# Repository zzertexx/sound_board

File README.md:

# Soundboard — 16-key Macropad

A custom 16-key macropad built with a Seeed Studio XIAO RP2040, per-key LEDs, and a 0.91" OLED display. Made for [Hack Club](https://hackclub.com/).

---

## Features

- 16 MX-compatible switches in a 4×4 matrix
- Per-key SK6812 MINI-E RGB LEDs
- 0.91" OLED display
- Seeed Studio XIAO RP2040 microcontroller
- QMK firmware
- 3D printed case with sandwitch mounting

---

## Bill of Materials

| Component | Quantity |
|---|---|
| Seeed Studio XIAO RP2040 | 1 |
| MX-style switches | 16 |
| 1N4148 diodes | 16 |
| SK6812 MINI-E LEDs | 16 |
| 0.91" OLED display | 1 |
| DSA white blank keycaps | 16 |
| Resistor 330 ohms | 1 |
| M3x16mm screws | 4 |
| M3x5x4mm heatset inserts | 4 |

---

## Pin Assignment

| Pin | Signal |
|---|---|
| GP0 (PA02) | Row 0 |
| GP1 (PA4) | Row 1 |
| GP2 (PA10) | Row 2 |
| GP3 (PA11) | Row 3 |
| GP4 (PA8 SDA) | OLED SDA |
| GP5 (PA9 SCL) | OLED SCL |
| GP6 (PB08) | Column 0 |
| GP7 (PB09) | Column 1 |
| GP8 (PA7 SCK) | Column 2 |
| GP9 (PA5 MISO) | Column 3 |
| GP10 (PA6 MOSI) | LED Data |

---

## Schematic & PCB

Designed in KiCad 9.0. All source files are in the PCB directory.

- 4×4 keyboard matrix with diodes
- SK6812 MINI-E LEDs placed on bottom layer under each switch
- OLED connected via I2C
- Resistor on GP10 rail for LED stability

---

## Images

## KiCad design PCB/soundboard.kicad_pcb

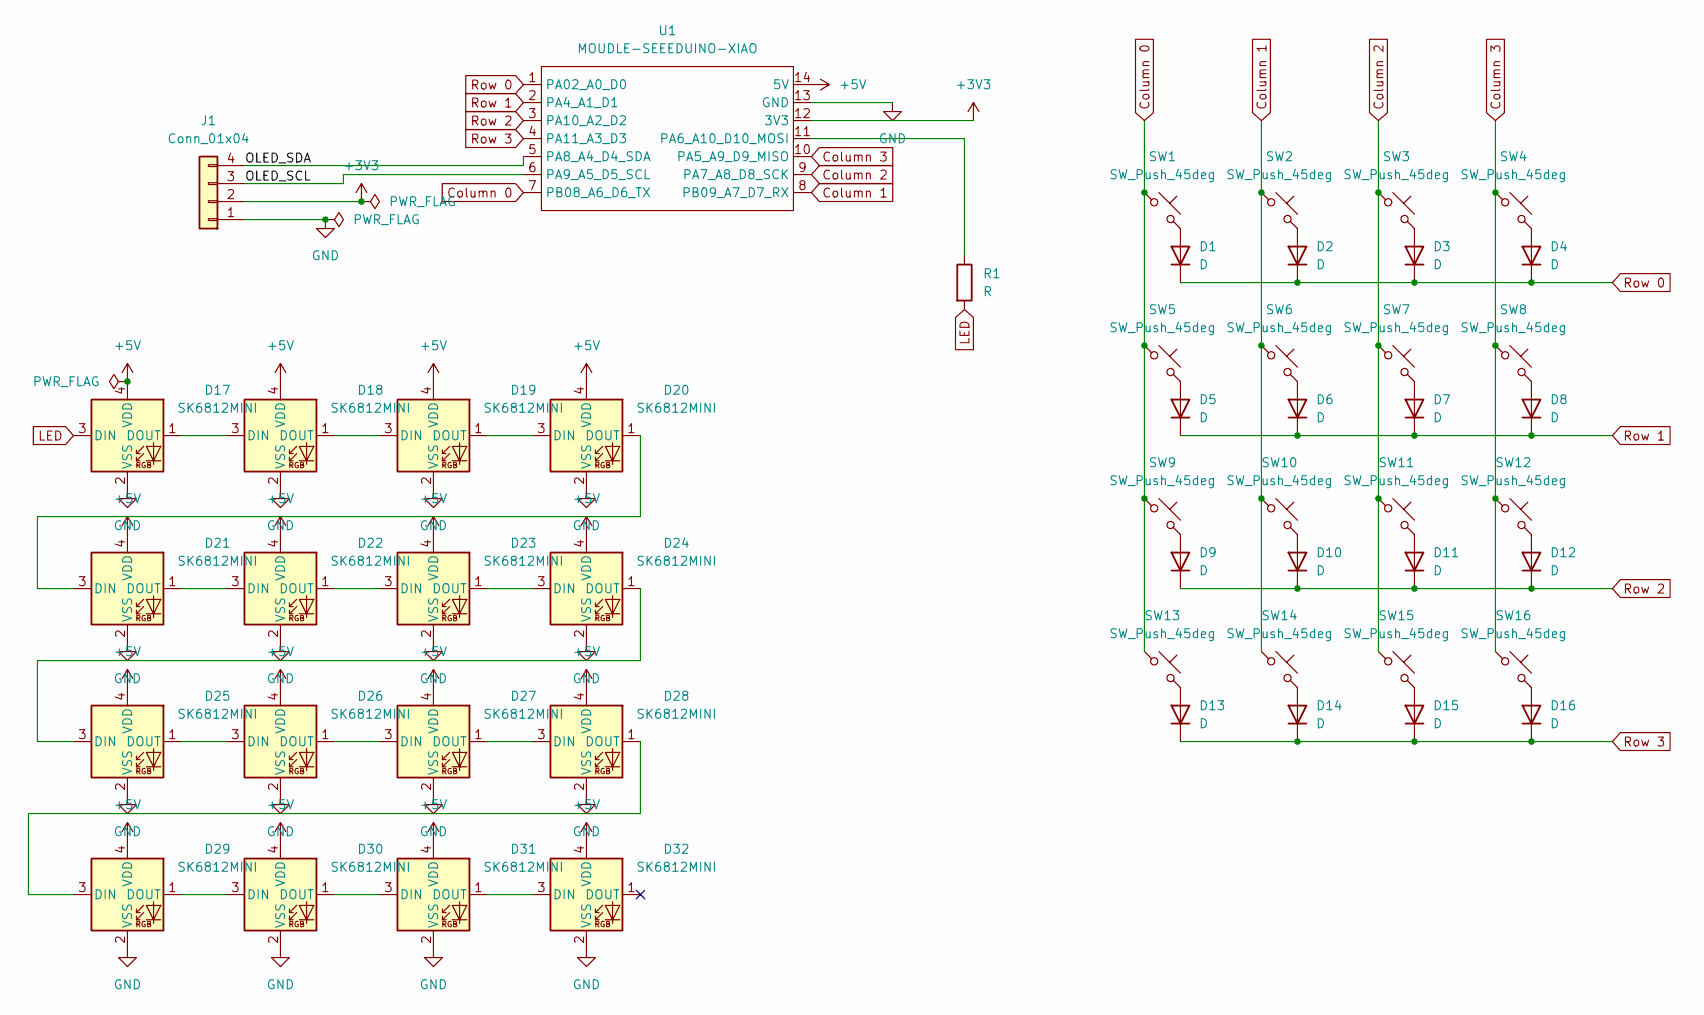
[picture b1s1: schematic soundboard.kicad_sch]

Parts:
D1, D2, D3, D4, D5, D6, D7, D8, D9, D10, D11, D12, D13, D14, D15, D16: D; D_DO-35_SOD27_P7.62mm_Horizontal
D17, D18, D19, D20, D21, D22, D23, D24, D25, D26, D27, D28, D29, D30, D31, D32: SK6812MINI; SK6812MINI-E_fixed
J1: Conn_01x04; PinHeader_1x04_P2.54mm_Vertical
R1: R; R_0805_2012Metric
SW1, SW2, SW3, SW4, SW5, SW6, SW7, SW8, SW9, SW10, SW11, SW12, SW13, SW14, SW15, SW16: SW_Push_45deg; SW_Cherry_MX_1.00u_PCB
U1: MOUDLE-SEEEDUINO-XIAO; XIAO-Generic-Hybrid-14P-2.54-21X17.8MM

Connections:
+3V3: J1.2, U1.12 (3V3)
+5V: D17.4 (VDD), D18.4 (VDD), D19.4 (VDD), D20.4 (VDD), D21.4 (VDD), D22.4 (VDD), D23.4 (VDD), D24.4 (VDD), D25.4 (VDD), D26.4 (VDD), D27.4 (VDD), D28.4 (VDD), D29.4 (VDD), D30.4 (VDD), D31.4 (VDD), D32.4 (VDD), U1.14 (5V)
/OLED_SCL: J1.3, U1.6 (PA9_A5_D5_SCL)
/OLED_SDA: J1.4, U1.5 (PA8_A4_D4_SDA)
Column 0: SW1.1, SW5.1, SW9.1, SW13.1, U1.7 (PB08_A6_D6_TX)
Column 1: SW2.1, SW6.1, SW10.1, SW14.1, U1.8 (PB09_A7_D7_RX)
Column 2: SW3.1, SW7.1, SW11.1, SW15.1, U1.9 (PA7_A8_D8_SCK)
Column 3: SW4.1, SW8.1, SW12.1, SW16.1, U1.10 (PA5_A9_D9_MISO)
GND: D17.2 (VSS), D18.2 (VSS), D19.2 (VSS), D20.2 (VSS), D21.2 (VSS), D22.2 (VSS), D23.2 (VSS), D24.2 (VSS), D25.2 (VSS), D26.2 (VSS), D27.2 (VSS), D28.2 (VSS), D29.2 (VSS), D30.2 (VSS), D31.2 (VSS), D32.2 (VSS), J1.1, U1.13 (GND)
LED: D17.3 (DIN), R1.2
unnamed: D1.2 (A), SW1.2
unnamed: D2.2 (A), SW2.2
unnamed: D3.2 (A), SW3.2
unnamed: D4.2 (A), SW4.2
unnamed: D5.2 (A), SW5.2
unnamed: D6.2 (A), SW6.2
unnamed: D7.2 (A), SW7.2
unnamed: D8.2 (A), SW8.2
unnamed: D9.2 (A), SW9.2
unnamed: D10.2 (A), SW10.2
unnamed: D11.2 (A), SW11.2
unnamed: D12.2 (A), SW12.2
unnamed: D13.2 (A), SW13.2
unnamed: D14.2 (A), SW14.2
unnamed: D15.2 (A), SW15.2
unnamed: D16.2 (A), SW16.2
unnamed: D17.1 (DOUT), D18.3 (DIN)
unnamed: D18.1 (DOUT), D19.3 (DIN)
unnamed: D19.1 (DOUT), D20.3 (DIN)
unnamed: D20.1 (DOUT), D21.3 (DIN)
unnamed: D21.1 (DOUT), D22.3 (DIN)
unnamed: D22.1 (DOUT), D23.3 (DIN)
unnamed: D23.1 (DOUT), D24.3 (DIN)
unnamed: D24.1 (DOUT), D25.3 (DIN)
unnamed: D25.1 (DOUT), D26.3 (DIN)
unnamed: D26.1 (DOUT), D27.3 (DIN)
unnamed: D27.1 (DOUT), D28.3 (DIN)
unnamed: D28.1 (DOUT), D29.3 (DIN)
unnamed: D29.1 (DOUT), D30.3 (DIN)
unnamed: D30.1 (DOUT), D31.3 (DIN)
unnamed: D31.1 (DOUT), D32.3 (DIN)
unnamed: R1.1, U1.11 (PA6_A10_D10_MOSI)
Row 0: D1.1 (K), D2.1 (K), D3.1 (K), D4.1 (K), U1.1 (PA02_A0_D0)
Row 1: D5.1 (K), D6.1 (K), D7.1 (K), D8.1 (K), U1.2 (PA4_A1_D1)
Row 2: D9.1 (K), D10.1 (K), D11.1 (K), D12.1 (K), U1.3 (PA10_A2_D2)
Row 3: D13.1 (K), D14.1 (K), D15.1 (K), D16.1 (K), U1.4 (PA11_A3_D3)

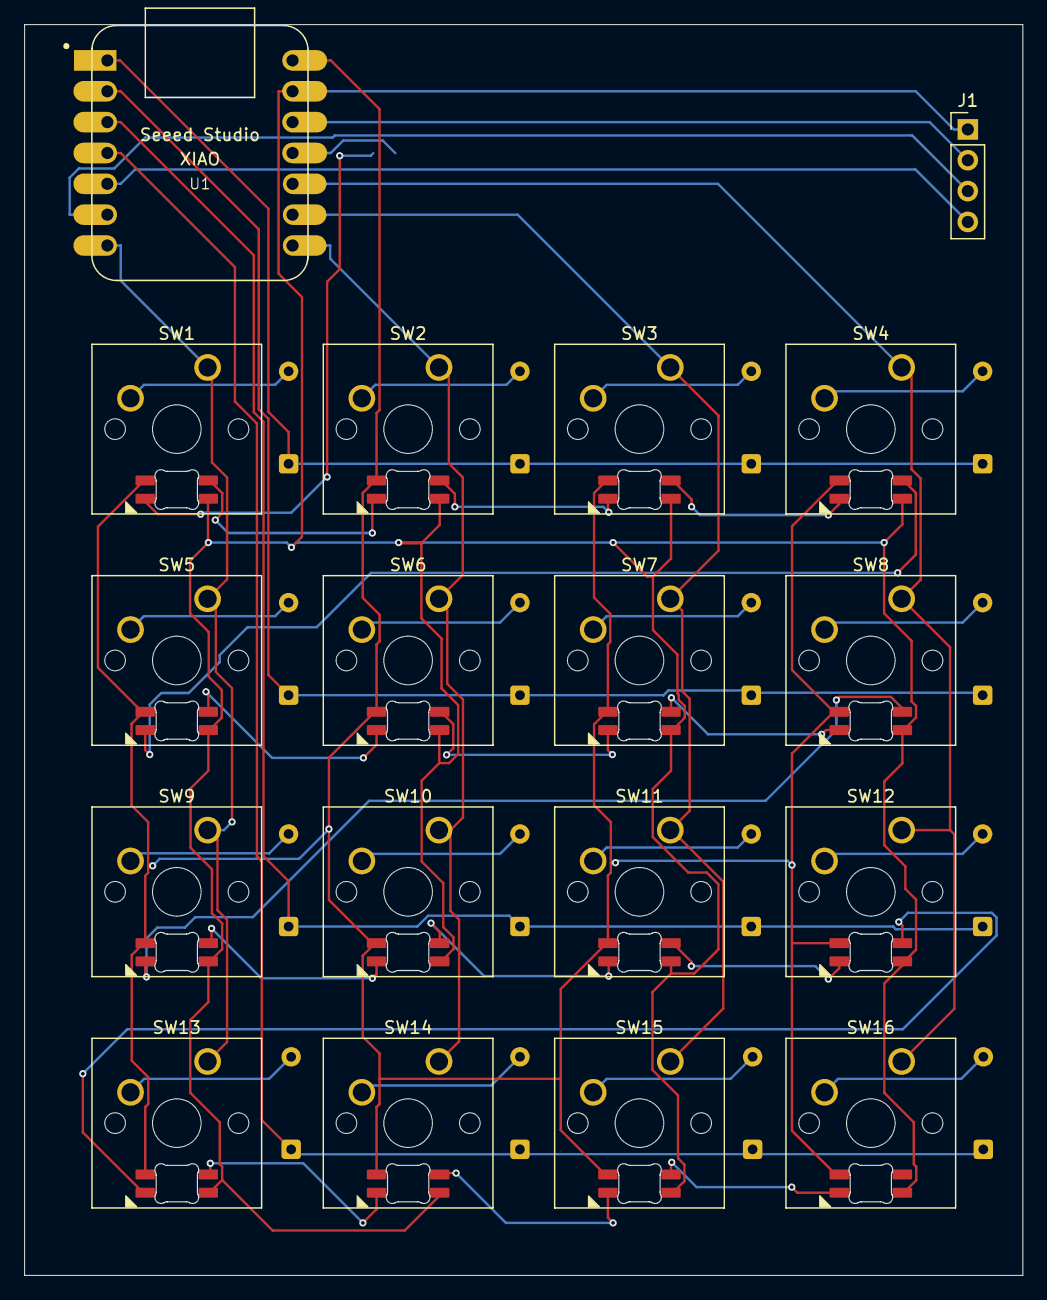
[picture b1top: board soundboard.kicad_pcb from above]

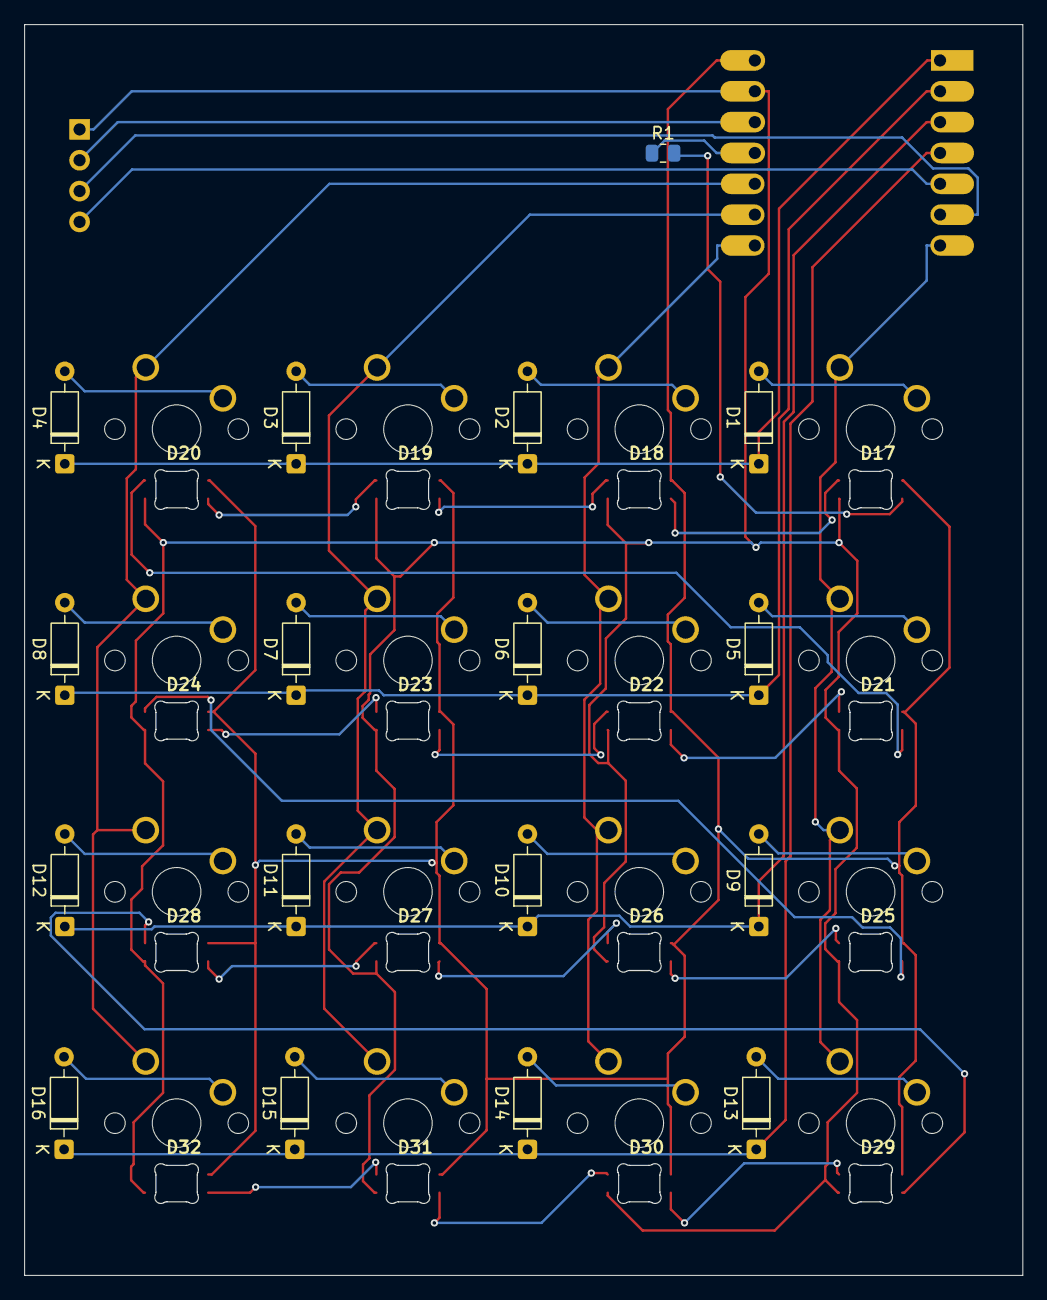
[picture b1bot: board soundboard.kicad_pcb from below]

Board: 2 copper layers, 82.1 x 102.9 mm, 51 parts (33 on the bottom side), 46 nets.

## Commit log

2026-03-23 Initialize project
2026-03-23 finished KiCad
2026-03-30 firmware
